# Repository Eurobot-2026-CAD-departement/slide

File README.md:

# Slide — final Eurobot 2026 robot

This repository contains the **official and final CAD** of the Eurobot 2026 Aerobotix robot.

The full assembly of the robot is `Slide final CAD.SLDASM` (stored with Git LFS). Each section of the design is in its own folder inside the assembly; folder and part names should be self-explanatory from there.

> For future reference: **zo7li9a = Slide** :)

## Contents
- `Slide final CAD.SLDASM`, `slide left/right.SLDASM`, `single slide complete.SLDASM`, `hinge left side.SLDASM` — assemblies
- `piece util/` — **most useful folder**: CAD of common pieces (motors, wheels, pumps, pneumatic fittings, ...). It will probably save you a lot of time. (Also available on its own as [slide-piece-util](https://github.com/Eurobot-2026-CAD-departement/slide-piece-util).)
- `3d printing/` — files for 3D printed parts
- `CNC lazer cutting/`, `CNC machining/` — laser-cutting and machining files / drawings
- `PCBs/` — KiCad projects of the electronics (MOSFET board, relay board, servo board, distribution board, ESP motors 2.0, PAMI ESP32, programming board, ...)
- `lidar support/`, `hinges/`, `pulley double action/`, `prototype/`, `essay 1/`, `missing_parts/` — sub-mechanisms and trials
- `slide urdf files/`, `URDFExporter/` — URDF export of the robot (SW2URDF)

Questions? Contact **Jihed Silini**.

Thank you for your attention to this file!

---

Part of the CAD work of the **Aerobotix (INSAT, Tunisia) Eurobot 2026 team** — see the [organization](https://github.com/Eurobot-2026-CAD-departement) for the other repositories. Files are mainly SolidWorks (`.SLDPRT` / `.SLDASM`) with STEP / STL / DXF exports. Released under the [MIT License](LICENSE). Questions about anything unclear? Contact a team member.

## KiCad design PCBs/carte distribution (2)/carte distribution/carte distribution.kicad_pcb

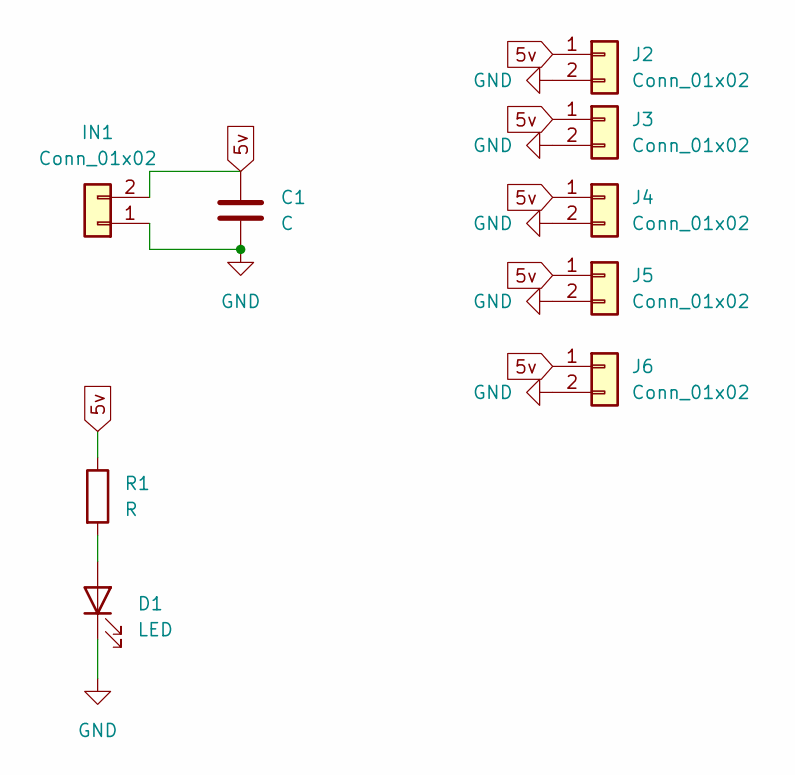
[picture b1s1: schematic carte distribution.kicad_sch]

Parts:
C1: C; C_Radial_D6.3mm_H5.0mm_P2.50mm
D1: LED; LED_D4.0mm
IN1: Conn_01x02; TerminalBlock_MaiXu_MX126-5.0-02P_1x02_P5.00mm
J2, J3, J4, J5, J6: Conn_01x02; TerminalBlock_MaiXu_MX126-5.0-02P_1x02_P5.00mm
R1: R; R_Axial_DIN0207_L6.3mm_D2.5mm_P7.62mm_Horizontal

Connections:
5v: C1.1, IN1.2, J2.1, J3.1, J4.1, J5.1, J6.1, R1.1
GND: C1.2, D1.1 (K), IN1.1, J2.2, J3.2, J4.2, J5.2, J6.2
unnamed: D1.2 (A), R1.2

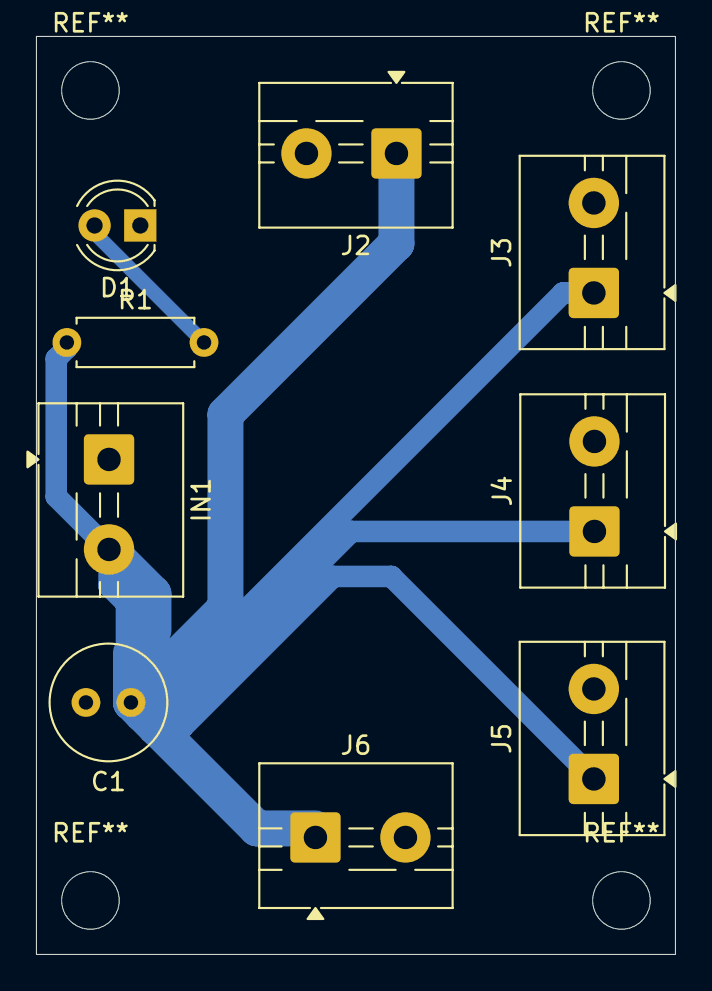
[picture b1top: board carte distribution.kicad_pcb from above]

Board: 2 copper layers, 35.5 x 51.0 mm, 9 parts (0 on the bottom side), 3 nets.

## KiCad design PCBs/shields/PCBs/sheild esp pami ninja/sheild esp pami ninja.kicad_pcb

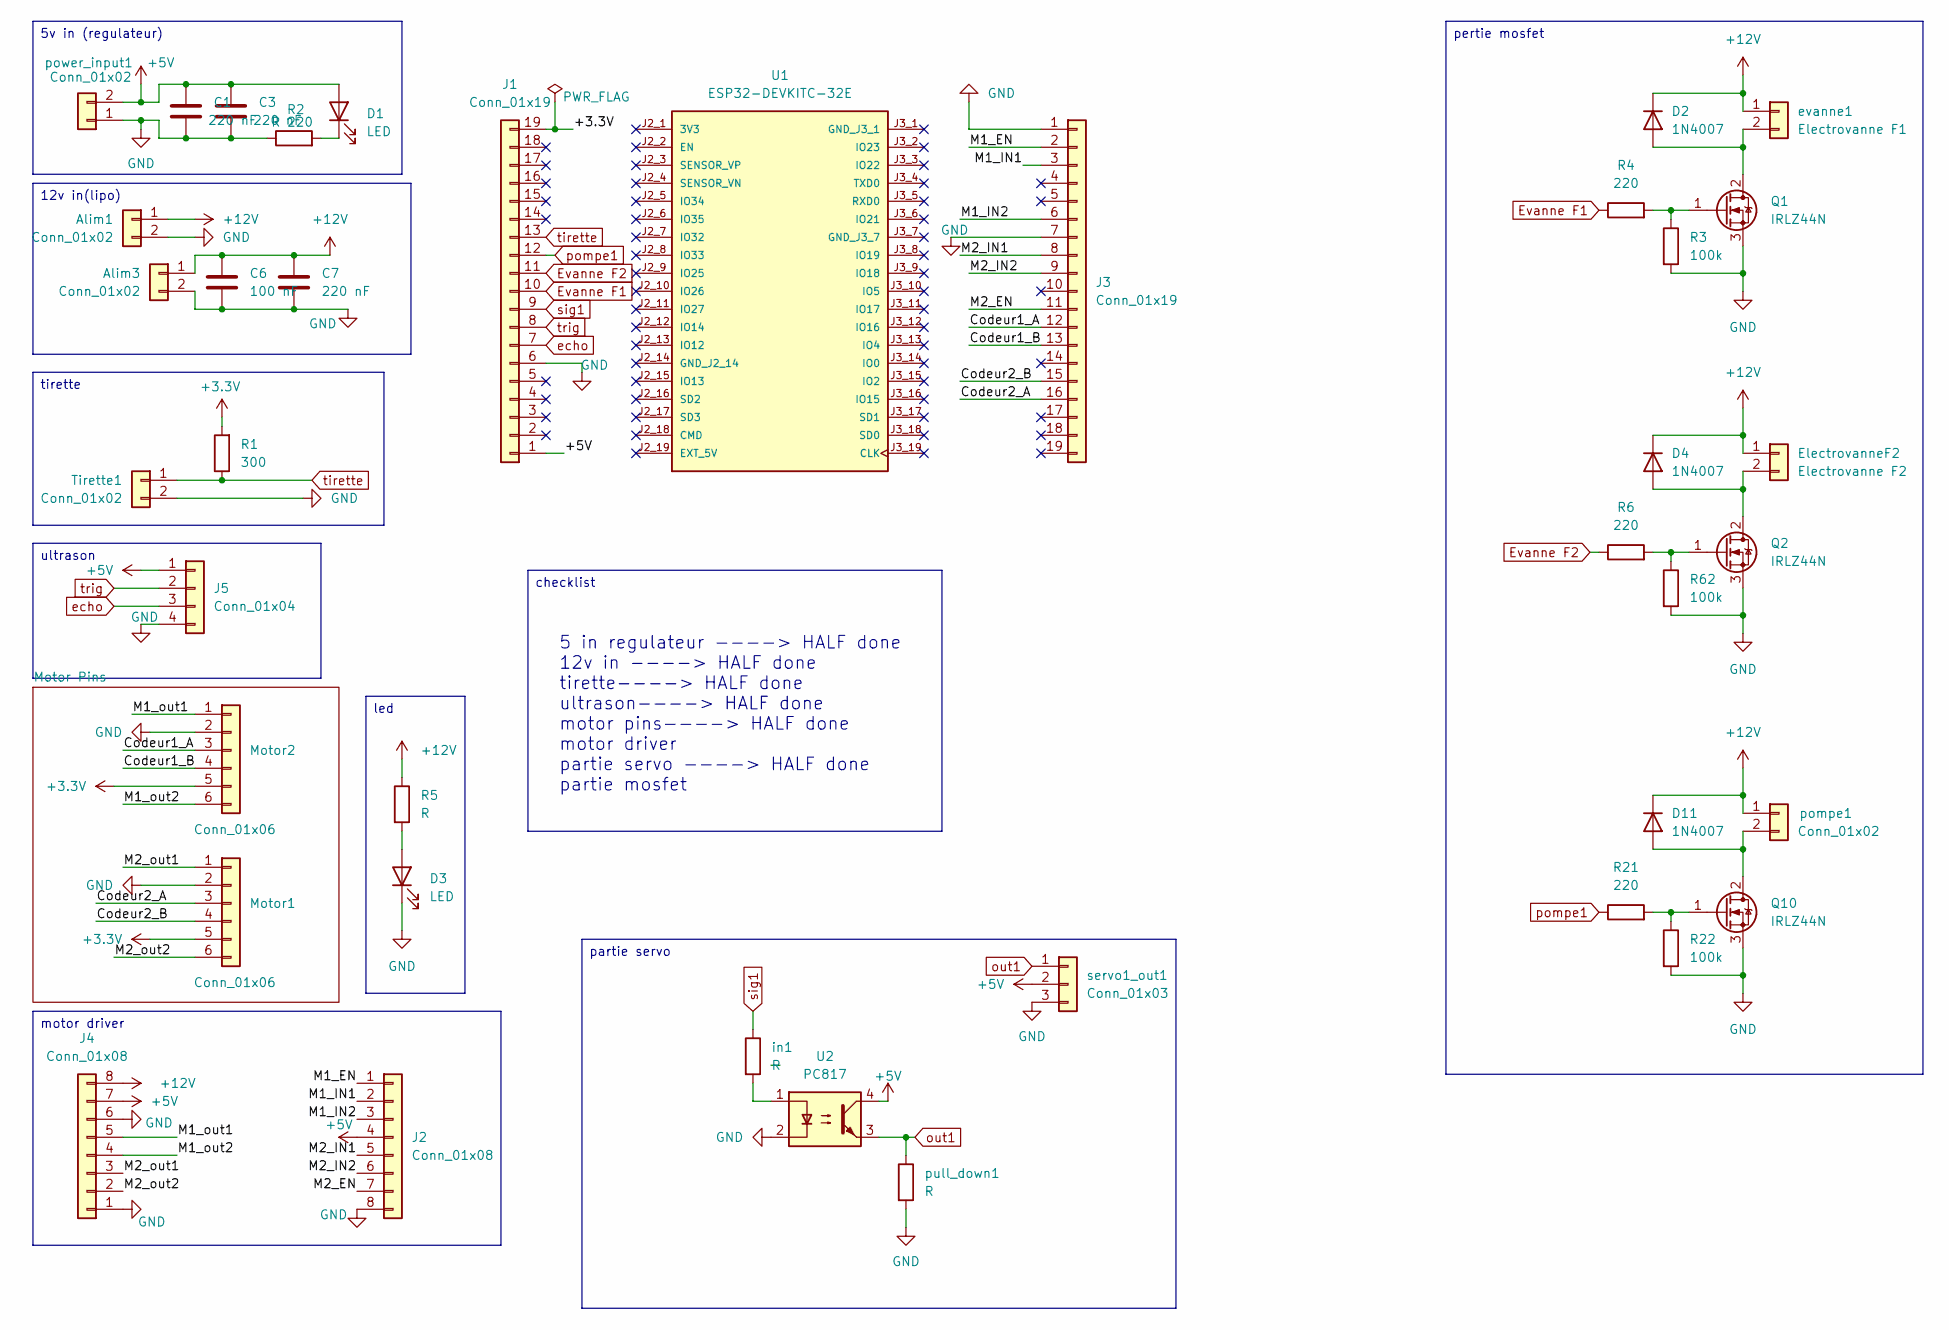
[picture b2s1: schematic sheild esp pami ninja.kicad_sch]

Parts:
Alim1, Alim3: Conn_01x02; TerminalBlock_MaiXu_MX126-5.0-02P_1x02_P5.00mm
C1, C3, C7: 220 nF; C_Radial_D6.3mm_H5.0mm_P2.50mm
C6: 100 nF; C_Radial_D6.3mm_H5.0mm_P2.50mm
D1, D3: LED; LED_D4.0mm
D2, D4, D11: 1N4007; D_DO-41_SOD81_P10.16mm_Horizontal
ElectrovanneF2: Electrovanne F2; JST_XH_B2B-XH-A_1x02_P2.50mm_Vertical
J1, J3: Conn_01x19; PinSocket_1x19_P2.54mm_Vertical
J2, J4: Conn_01x08; PinSocket_1x08_P2.54mm_Vertical
J5: Conn_01x04; PinHeader_1x04_P2.54mm_Vertical
Motor1, Motor2: Conn_01x06; PinHeader_1x06_P2.54mm_Vertical
Q1, Q2, Q10: IRLZ44N; TO-220-3_Vertical
R1: 300; R_Axial_DIN0207_L6.3mm_D2.5mm_P7.62mm_Horizontal
R2: R 220; R_Axial_DIN0207_L6.3mm_D2.5mm_P7.62mm_Horizontal
R3, R22, R62: 100k; R_Axial_DIN0207_L6.3mm_D2.5mm_P7.62mm_Horizontal
R4, R6, R21: 220; R_Axial_DIN0207_L6.3mm_D2.5mm_P7.62mm_Horizontal
R5: R; R_Axial_DIN0207_L6.3mm_D2.5mm_P7.62mm_Horizontal
Tirette1: Conn_01x02; PinHeader_1x02_P2.54mm_Vertical
U1: ESP32-DEVKITC-32E; PARTREV 1.4
U2: PC817; DIP-4_W7.62mm
evanne1: Electrovanne F1; JST_XH_B2B-XH-A_1x02_P2.50mm_Vertical
in1: R; R_Axial_DIN0207_L6.3mm_D2.5mm_P7.62mm_Horizontal
pompe1: Conn_01x02; JST_XH_B2B-XH-A_1x02_P2.50mm_Vertical
power_input1: Conn_01x02; TerminalBlock_MaiXu_MX126-5.0-02P_1x02_P5.00mm
pull_down1: R; R_Axial_DIN0207_L6.3mm_D2.5mm_P7.62mm_Horizontal
servo1_out1: Conn_01x03; PinHeader_1x03_P2.54mm_Vertical

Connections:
+3.3V: J1.19, Motor1.5, Motor2.5, R1.2
+5V: C1.1, C3.1, D1.2 (A), J1.1, J2.4, J4.7, J5.1, U2.4, power_input1.2, servo1_out1.2
+12V: Alim1.1, Alim3.1, C6.1, C7.1, D2.1 (K), D4.1 (K), D11.1 (K), ElectrovanneF2.1, J4.8, R5.1, evanne1.1, pompe1.1
/Codeur1_A: J3.12, Motor2.3
/Codeur1_B: J3.13, Motor2.4
/Codeur2_A: J3.16, Motor1.3
/Codeur2_B: J3.15, Motor1.4
/M1_EN: J2.1, J3.2
/M1_IN1: J2.2, J3.3
/M1_IN2: J2.3, J3.6
/M1_out1: J4.5, Motor2.1
/M1_out2: J4.4, Motor2.6
/M2_EN: J2.7, J3.11
/M2_IN1: J2.5, J3.8
/M2_IN2: J2.6, J3.9
/M2_out1: J4.3, Motor1.1
/M2_out2: J4.2, Motor1.6
Evanne F1: J1.10, R4.1
Evanne F2: J1.11, R6.1
GND: Alim1.2, Alim3.2, C1.2, C3.2, C6.2, C7.2, D3.1 (K), J1.6, J2.8, J3.1, J3.7, J4.1, J4.6, J5.4, Motor1.2, Motor2.2, Q1.3 (S), Q2.3 (S), Q10.3 (S), R2.1, R3.2, R22.2, R62.2, Tirette1.2, U2.2, power_input1.1, pull_down1.2, servo1_out1.3
unnamed: D1.1 (K), R2.2
unnamed: D2.2 (A), Q1.2 (D), evanne1.2
unnamed: D3.2 (A), R5.2
unnamed: D4.2 (A), ElectrovanneF2.2, Q2.2 (D)
unnamed: D11.2 (A), Q10.2 (D), pompe1.2
unnamed: Q1.1 (G), R3.1, R4.2
unnamed: Q2.1 (G), R6.2, R62.1
unnamed: Q10.1 (G), R21.2, R22.1
unnamed: U2.1, in1.2
echo: J1.7, J5.3
out1: U2.3, pull_down1.1, servo1_out1.1
pompe1: J1.12, R21.1
sig1: J1.9, in1.1
tirette: J1.13, R1.1, Tirette1.1
trig: J1.8, J5.2

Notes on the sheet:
5 in regulateur ----> HALF done 12v in ----> HALF done tirette----> HALF done ultrason----> HALF done motor pins----> HALF done motor driver partie servo ----> HALF done partie mosfet
pertie mosfet
5v in (regulateur)
checklist
ultrason
tirette
led
12v in(lipo)
partie servo
motor driver

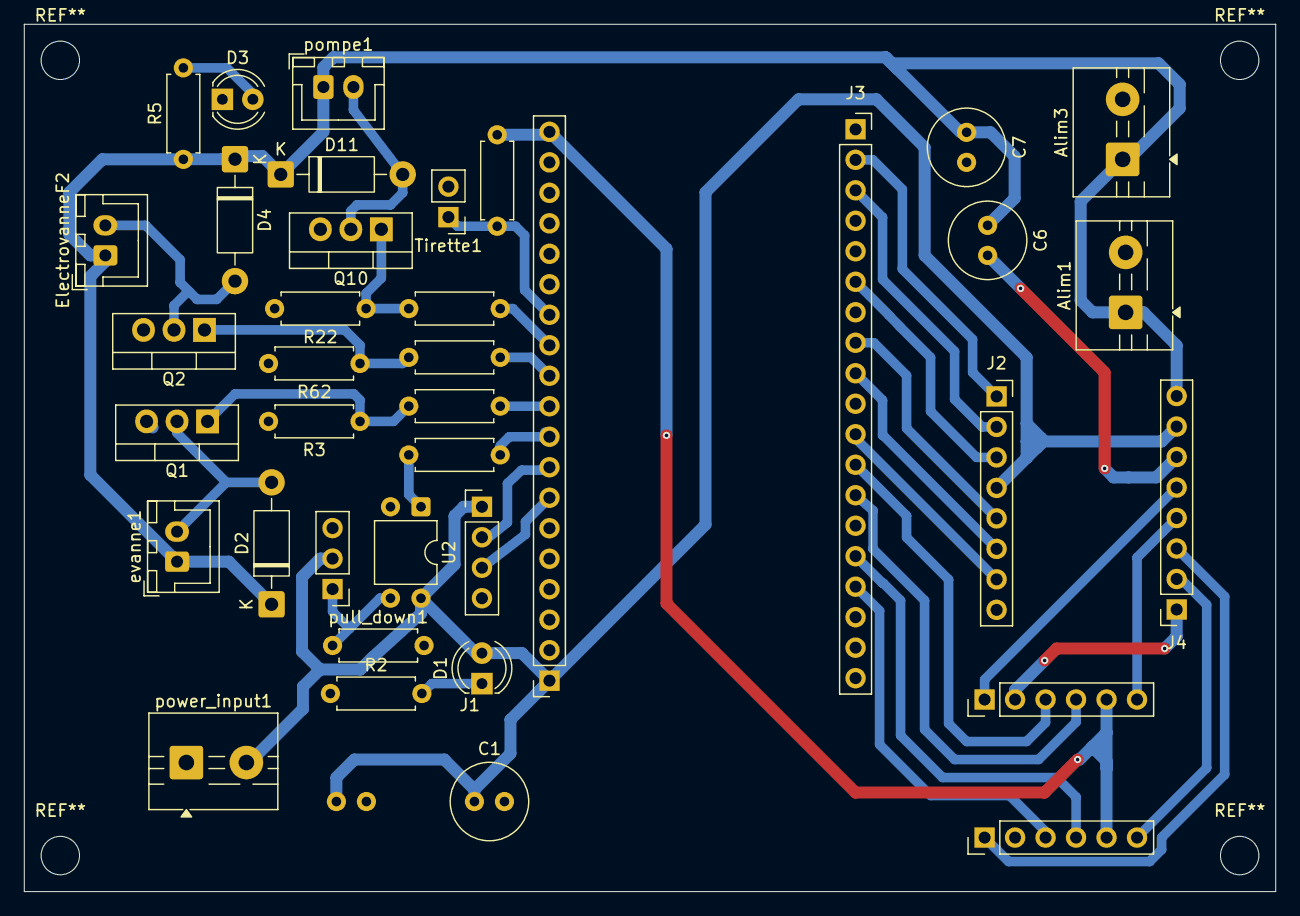
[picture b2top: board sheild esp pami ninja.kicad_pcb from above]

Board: 2 copper layers, 104.2 x 72.2 mm, 39 parts (1 on the bottom side), 35 nets.

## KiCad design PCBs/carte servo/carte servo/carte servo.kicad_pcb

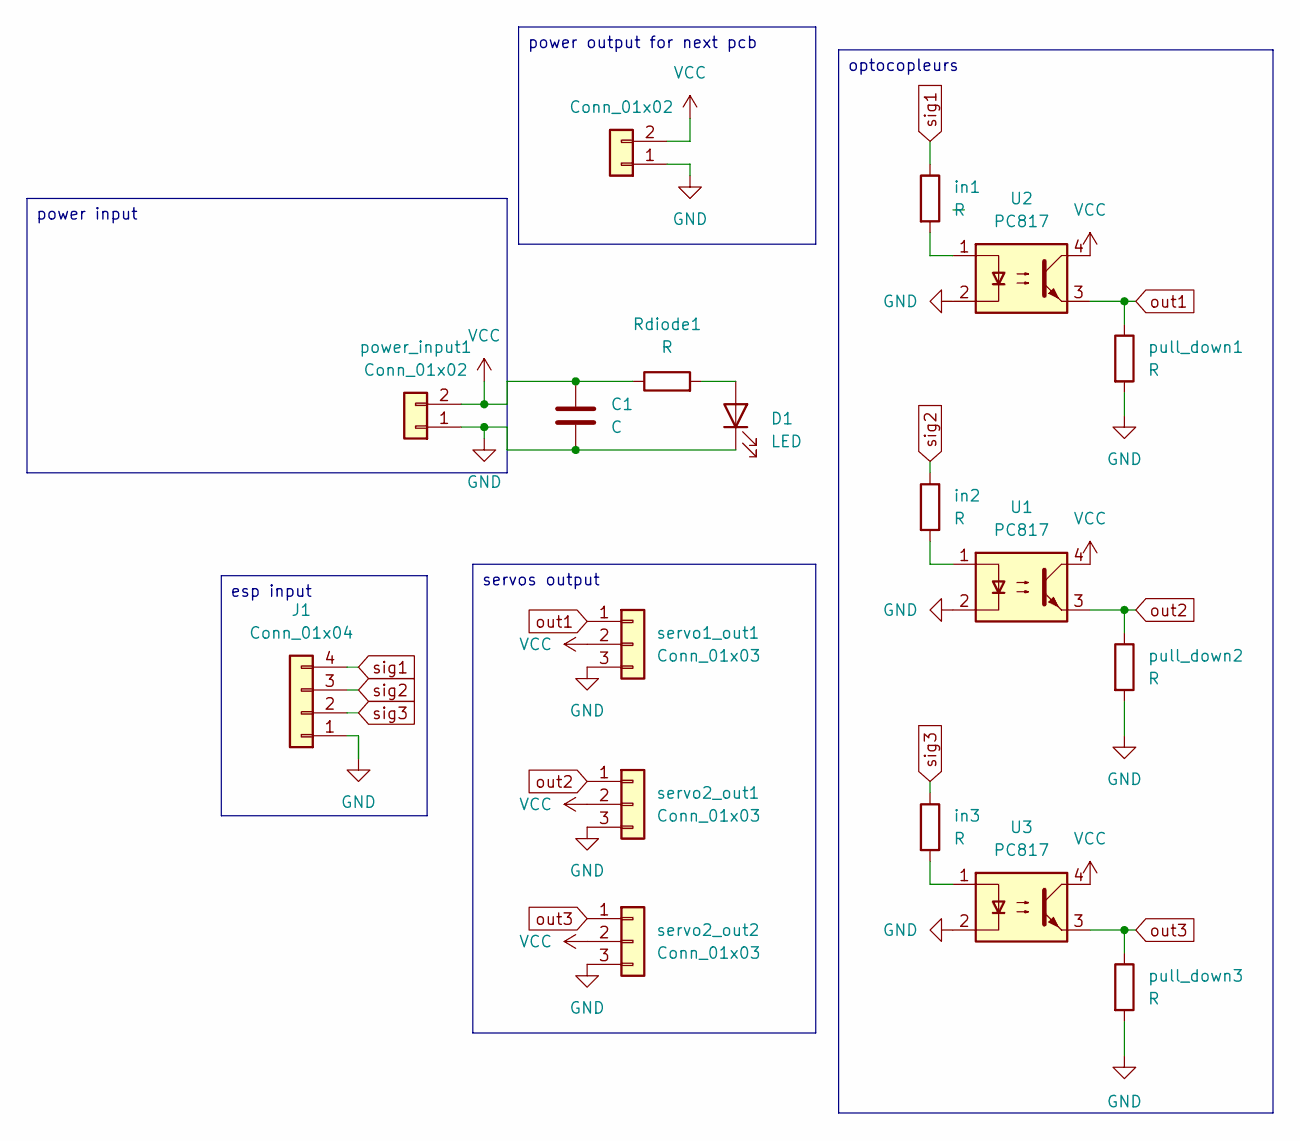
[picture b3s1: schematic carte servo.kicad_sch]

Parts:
C1: C; C_Radial_D6.3mm_H5.0mm_P2.50mm
D1: LED; LED_D4.0mm
J1: Conn_01x04; PinHeader_1x04_P2.54mm_Vertical
Rdiode1: R; R_Axial_DIN0207_L6.3mm_D2.5mm_P7.62mm_Horizontal
U1, U2, U3: PC817; DIP-4_W7.62mm
in1, in2, in3: R; R_Axial_DIN0207_L6.3mm_D2.5mm_P7.62mm_Horizontal
power_input1: Conn_01x02; TerminalBlock_MaiXu_MX126-5.0-02P_1x02_P5.00mm
power_output1: Conn_01x02; TerminalBlock_MaiXu_MX126-5.0-02P_1x02_P5.00mm
pull_down1, pull_down2, pull_down3: R; R_Axial_DIN0207_L6.3mm_D2.5mm_P7.62mm_Horizontal
servo1_out1, servo2_out1, servo2_out2: Conn_01x03; PinHeader_1x03_P2.54mm_Vertical

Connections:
GND: C1.2, D1.1 (K), J1.1, U1.2, U2.2, U3.2, power_input1.1, power_output1.1, pull_down1.2, pull_down2.2, pull_down3.2, servo1_out1.3, servo2_out1.3, servo2_out2.3
unnamed: D1.2 (A), Rdiode1.2
unnamed: U1.1, in2.2
unnamed: U2.1, in1.2
unnamed: U3.1, in3.2
VCC: C1.1, Rdiode1.1, U1.4, U2.4, U3.4, power_input1.2, power_output1.2, servo1_out1.2, servo2_out1.2, servo2_out2.2
out1: U2.3, pull_down1.1, servo1_out1.1
out2: U1.3, pull_down2.1, servo2_out1.1
out3: U3.3, pull_down3.1, servo2_out2.1
sig1: J1.4, in1.1
sig2: J1.3, in2.1
sig3: J1.2, in3.1

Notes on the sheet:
power input
optocopleurs
esp input
servos output
power output for next pcb

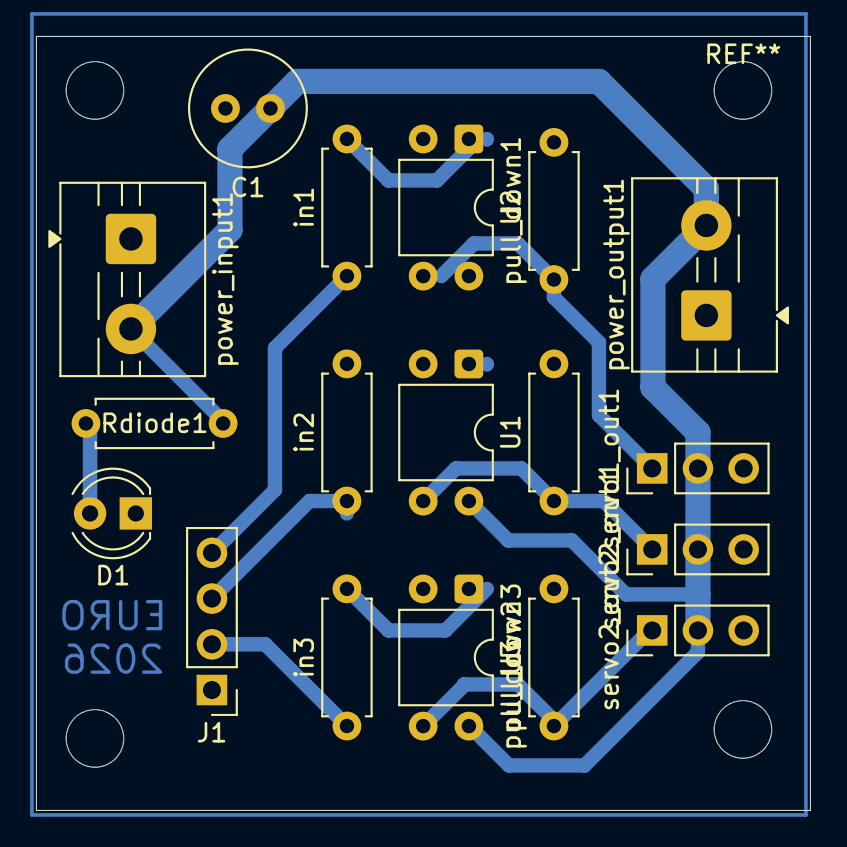
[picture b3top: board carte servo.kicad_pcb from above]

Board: 2 copper layers, 43.0 x 43.0 mm, 18 parts (0 on the bottom side), 12 nets.

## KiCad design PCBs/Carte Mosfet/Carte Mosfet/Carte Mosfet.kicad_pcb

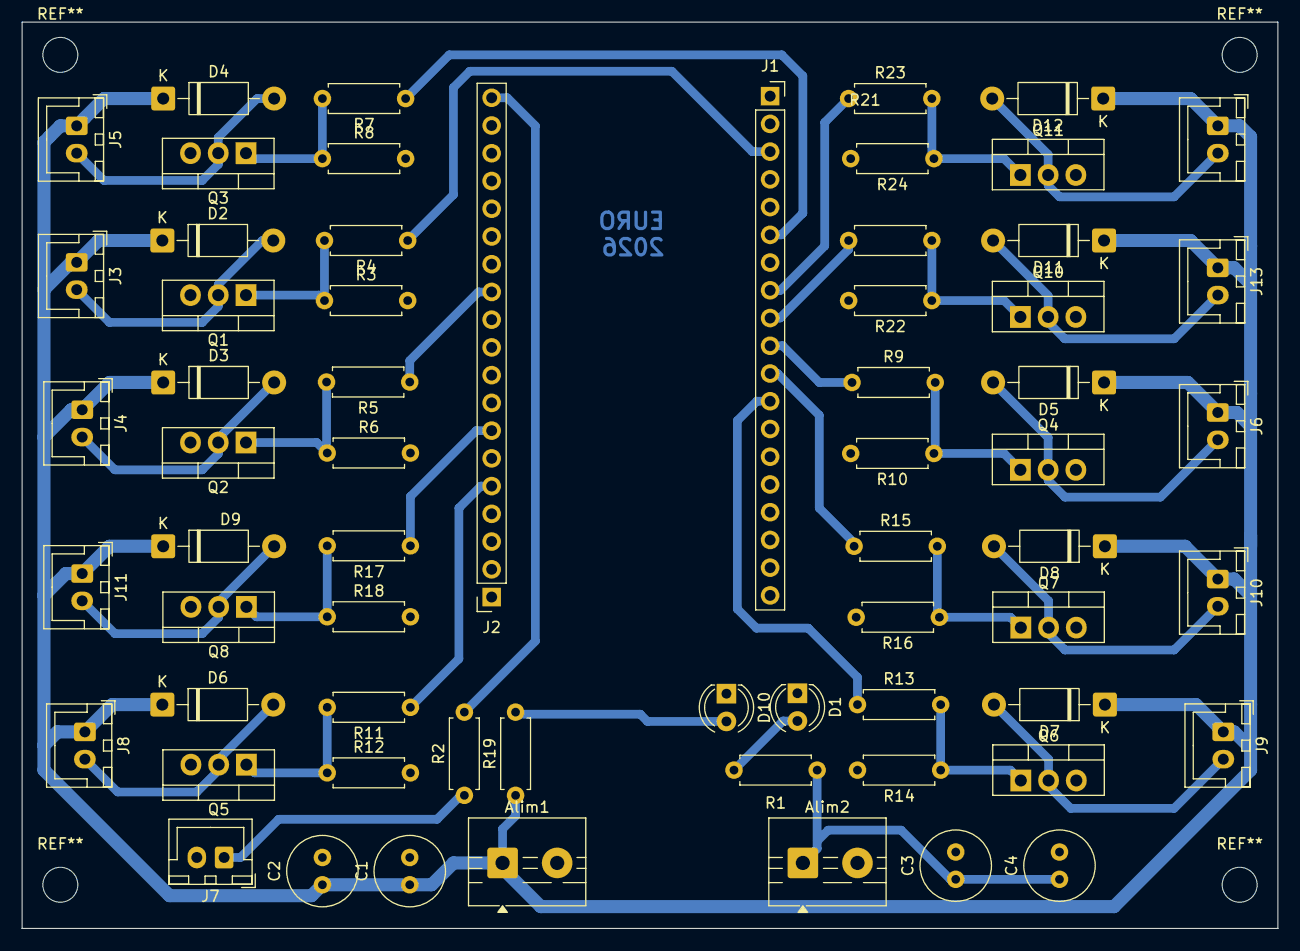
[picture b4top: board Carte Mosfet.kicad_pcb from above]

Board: 2 copper layers, 115.0 x 83.0 mm, 64 parts (0 on the bottom side), 37 nets.

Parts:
Alim1, Alim2: Conn_01x02; TerminalBlock_MaiXu_MX126-5.0-02P_1x02_P5.00mm
C1, C3: 100 nF; C_Radial_D6.3mm_H5.0mm_P2.50mm
C2, C4: 220 nF; C_Radial_D6.3mm_H5.0mm_P2.50mm
D1, D10: LED; LED_D4.0mm
D2, D3, D4, D5, D6, D7, D8, D9, D11, D12: 1N4007; D_DO-41_SOD81_P10.16mm_Horizontal
J1, J2: Conn_01x19; PinSocket_1x19_P2.54mm_Vertical
J3, J4, J5, J6, J8, J9, J10, J11, J13, J14: Conn_01x02; JST_XH_B2B-XH-A_1x02_P2.50mm_Vertical
J7: Conn_01x01; JST_XH_B2B-XH-A_1x02_P2.50mm_Vertical
Q1, Q2, Q3, Q4, Q5, Q6, Q7, Q8, Q10, Q11: IRLZ44N; TO-220-3_Vertical
R1, R19: R; R_Axial_DIN0207_L6.3mm_D2.5mm_P7.62mm_Horizontal
R2: 10k; R_Axial_DIN0207_L6.3mm_D2.5mm_P7.62mm_Horizontal
R3, R6, R8, R10, R12, R14, R16, R18, R22, R24: 100k; R_Axial_DIN0207_L6.3mm_D2.5mm_P7.62mm_Horizontal
R4, R5, R7, R9, R11, R13, R15, R17, R21, R23: 220; R_Axial_DIN0207_L6.3mm_D2.5mm_P7.62mm_Horizontal

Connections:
+3.3V: J2.19, R2.2
+5V: Alim2.1, C3.1, C4.1, J2.1, R1.1
+12V: Alim1.1, C1.1, C2.1, D2.1 (K), D3.1 (K), D4.1 (K), D5.1 (K), D6.1 (K), D7.1 (K), D8.1 (K), D9.1 (K), D11.1 (K), D12.1 (K), J3.1, J4.1, J5.1, J6.1, J8.1, J9.1, J10.1, J11.1, J13.1, J14.1, R19.1
Electrovanne B1: J2.5, R11.1
Electrovanne B2: J1.12, R13.1
Electrovanne B3: J1.11, R15.1
Electrovanne B4: J2.7, R17.1
Electrovanne F1: J1.3, R4.1
Electrovanne F2: J2.12, R5.1
Electrovanne F3: J1.6, R7.1
Electrovanne F4: J1.10, R9.1
GND: Alim1.2, Alim2.2, C1.2, C2.2, C3.2, C4.2, D1.1 (K), D10.1 (K), J1.1, J1.7, J2.6, Q1.3 (S), Q2.3 (S), Q3.3 (S), Q4.3 (S), Q5.3 (S), Q6.3 (S), Q7.3 (S), Q8.3 (S), Q10.3 (S), Q11.3 (S), R3.2, R6.2, R8.2, R10.2, R12.2, R14.2, R16.2, R18.2, R22.2, R24.2
unnamed: D1.2 (A), R1.2
unnamed: D2.2 (A), J3.2, Q1.2 (D)
unnamed: D3.2 (A), J4.2, Q2.2 (D)
unnamed: D4.2 (A), J5.2, Q3.2 (D)
unnamed: D5.2 (A), J6.2, Q4.2 (D)
unnamed: D6.2 (A), J8.2, Q5.2 (D)
unnamed: D7.2 (A), J9.2, Q6.2 (D)
unnamed: D8.2 (A), J10.2, Q7.2 (D)
unnamed: D9.2 (A), J11.2, Q8.2 (D)
unnamed: D10.2 (A), R19.2
unnamed: D11.2 (A), J13.2, Q10.2 (D)
unnamed: D12.2 (A), J14.2, Q11.2 (D)
unnamed: Q1.1 (G), R3.1, R4.2
unnamed: Q2.1 (G), R5.2, R6.1
unnamed: Q3.1 (G), R7.2, R8.1
unnamed: Q4.1 (G), R9.2, R10.1
unnamed: Q5.1 (G), R11.2, R12.1
unnamed: Q6.1 (G), R13.2, R14.1
unnamed: Q7.1 (G), R15.2, R16.1
unnamed: Q8.1 (G), R17.2, R18.1
unnamed: Q10.1 (G), R21.2, R22.1
unnamed: Q11.1 (G), R23.2, R24.1
Pump 1: J1.9, R21.1
Pump 2: J1.8, R23.1
en: J2.18, J7.1, R2.1

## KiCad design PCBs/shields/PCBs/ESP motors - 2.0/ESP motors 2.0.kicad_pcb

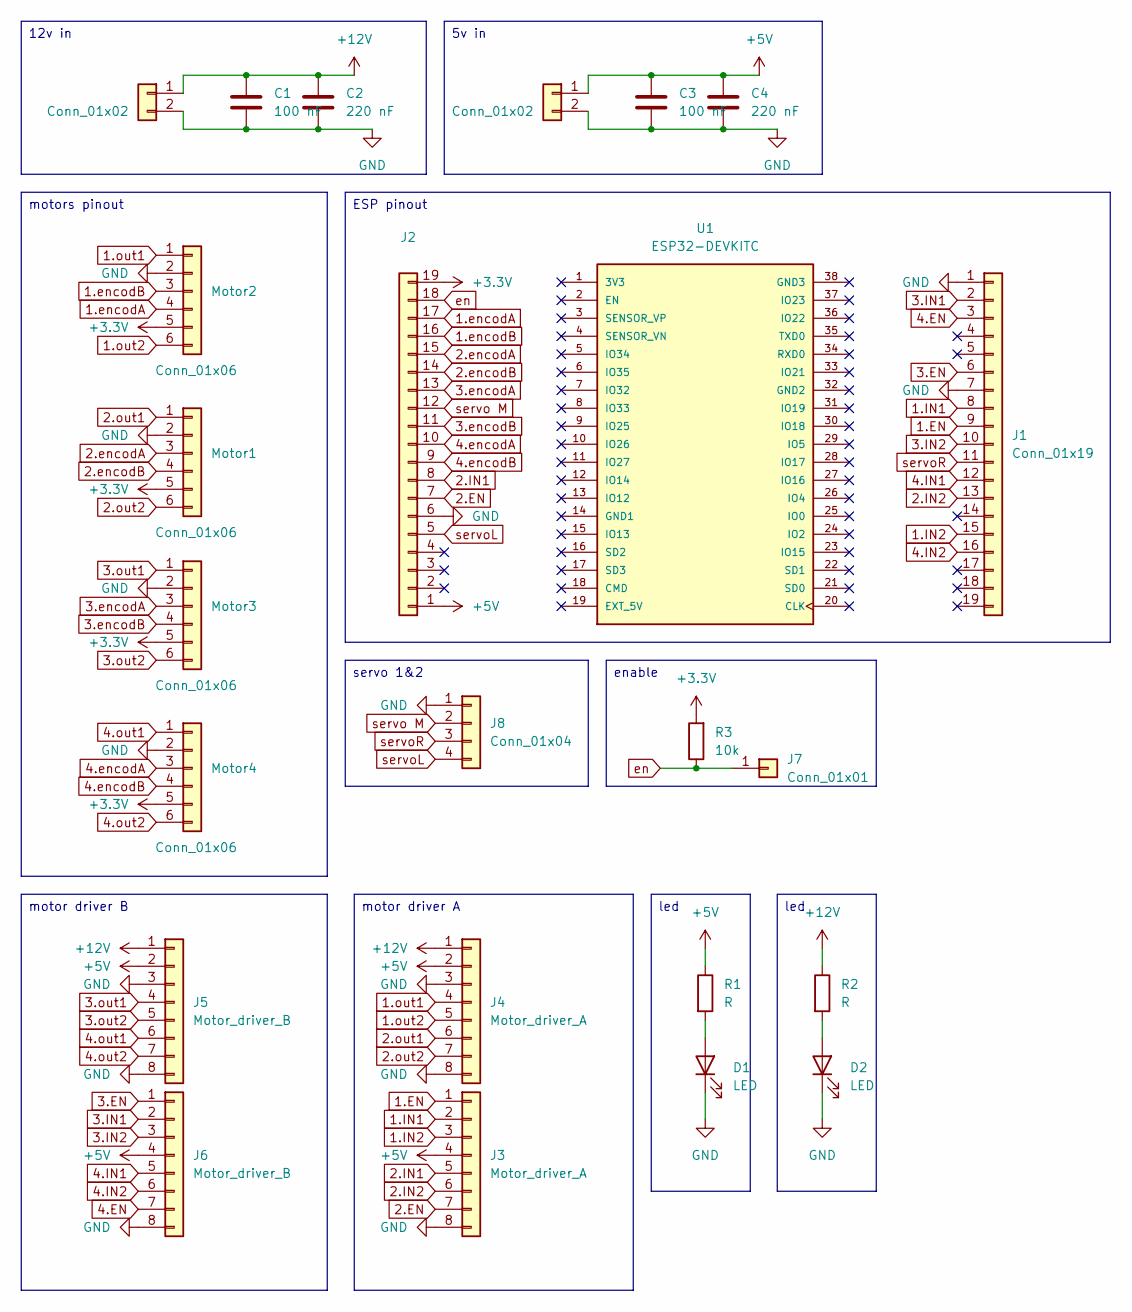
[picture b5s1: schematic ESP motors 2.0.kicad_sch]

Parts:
Alim1, Alim2: Conn_01x02; TerminalBlock_MaiXu_MX126-5.0-02P_1x02_P5.00mm
C1, C3: 100 nF; C_Radial_D6.3mm_H5.0mm_P2.50mm
C2, C4: 220 nF; C_Radial_D6.3mm_H5.0mm_P2.50mm
D1, D2: LED; LED_D4.0mm
J1, J2: Conn_01x19; PinSocket_1x19_P2.54mm_Vertical
J3, J4: Motor_driver_A; PinSocket_1x08_P2.54mm_Vertical
J5, J6: Motor_driver_B; PinSocket_1x08_P2.54mm_Vertical
J7: Conn_01x01; JST_XH_B2B-XH-A_1x02_P2.50mm_Vertical
J8: Conn_01x04; PinHeader_1x04_P2.54mm_Vertical
Motor1, Motor2, Motor3, Motor4: Conn_01x06; PinHeader_1x06_P2.54mm_Vertical
R1, R2: R; R_Axial_DIN0207_L6.3mm_D2.5mm_P7.62mm_Horizontal
R3: 10k; R_Axial_DIN0207_L6.3mm_D2.5mm_P7.62mm_Horizontal
U1: ESP32-DEVKITC; MODULE_ESP32-DEVKITC; PARTREV N/A

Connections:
1.EN: J1.9, J3.1
1.IN1: J1.8, J3.2
1.IN2: J1.15, J3.3
1.encodA: J2.17, Motor2.4
1.encodB: J2.16, Motor2.3
1.out1: J4.4, Motor2.1
1.out2: J4.5, Motor2.6
2.EN: J2.7, J3.7
2.IN1: J2.8, J3.5
2.IN2: J1.13, J3.6
2.encodA: J2.15, Motor1.3
2.encodB: J2.14, Motor1.4
2.out1: J4.6, Motor1.1
2.out2: J4.7, Motor1.6
3.EN: J1.6, J6.1
3.IN1: J1.2, J6.2
3.IN2: J1.10, J6.3
3.encodA: J2.13, Motor3.3
3.encodB: J2.11, Motor3.4
3.out1: J5.4, Motor3.1
3.out2: J5.5, Motor3.6
4.EN: J1.3, J6.7
4.IN1: J1.12, J6.5
4.IN2: J1.16, J6.6
4.encodA: J2.10, Motor4.3
4.encodB: J2.9, Motor4.4
4.out1: J5.6, Motor4.1
4.out2: J5.7, Motor4.6
+3.3V: J2.19, Motor1.5, Motor2.5, Motor3.5, Motor4.5, R3.2
+5V: Alim2.1, C3.1, C4.1, J2.1, J3.4, J4.2, J5.2, J6.4, R1.1
+12V: Alim1.1, C1.1, C2.1, J4.1, J5.1, R2.1
GND: Alim1.2, Alim2.2, C1.2, C2.2, C3.2, C4.2, D1.1 (K), D2.1 (K), J1.1, J1.7, J2.6, J3.8, J4.3, J4.8, J5.3, J5.8, J6.8, J8.1, Motor1.2, Motor2.2, Motor3.2, Motor4.2
unnamed: D1.2 (A), R1.2
unnamed: D2.2 (A), R2.2
en: J2.18, J7.1, R3.1
servo M: J2.12, J8.2
servoL: J2.5, J8.4
servoR: J1.11, J8.3

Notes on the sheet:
motor driver B
led
12v in
5v in
enable
motor driver A
servo 1&2
motors pinout
ESP pinout

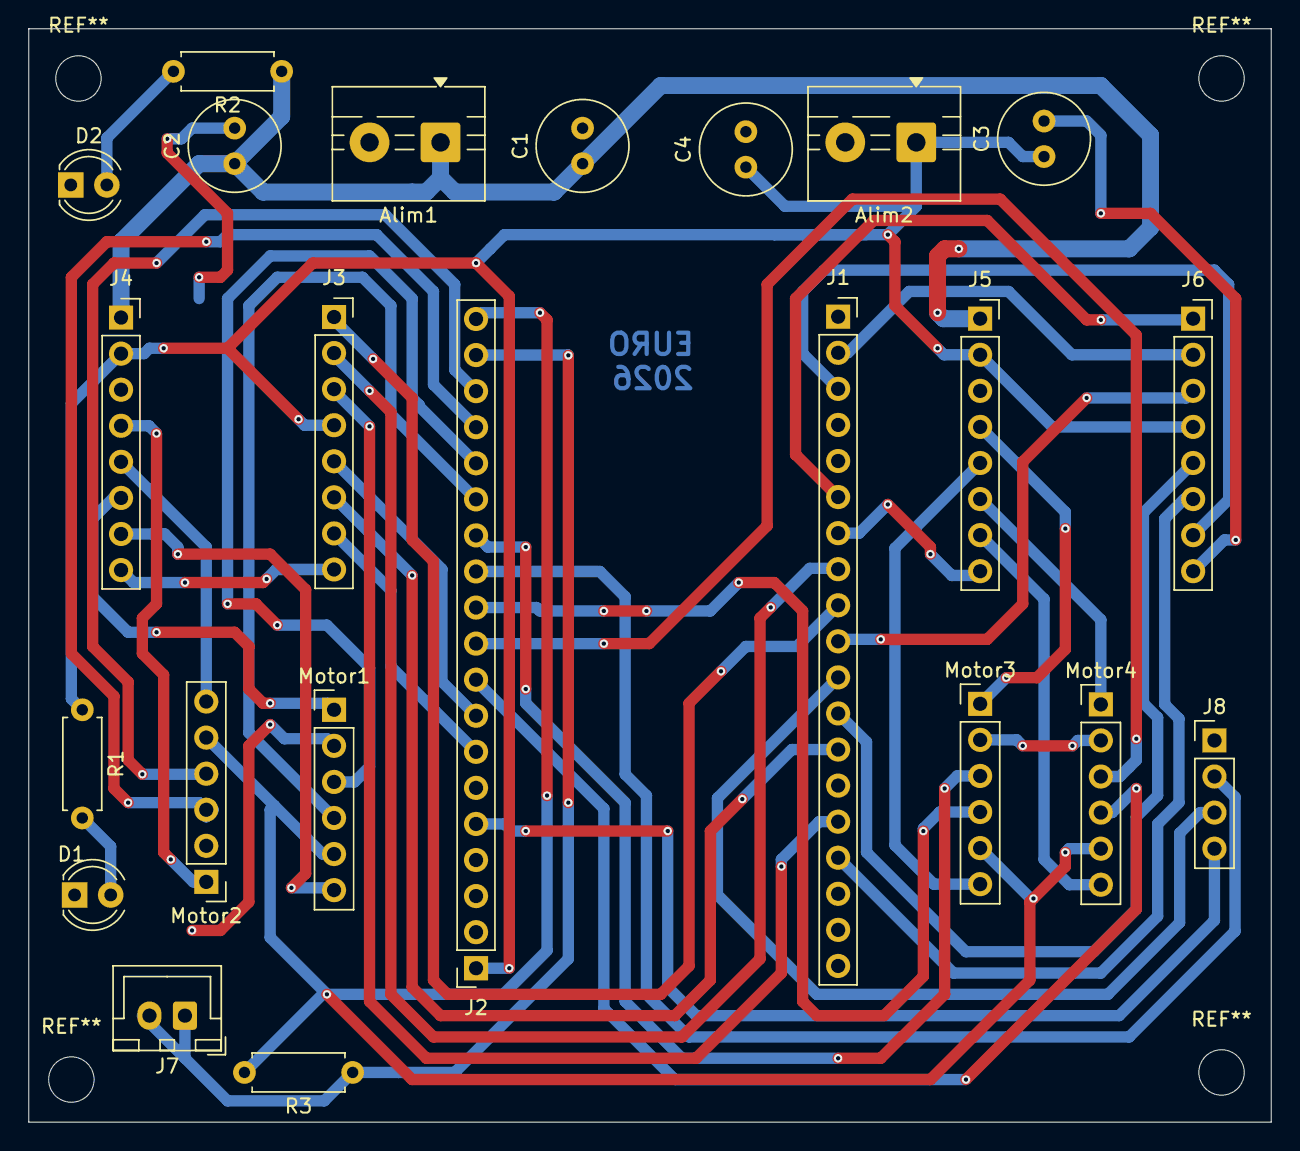
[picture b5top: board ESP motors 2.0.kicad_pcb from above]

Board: 2 copper layers, 87.5 x 77.0 mm, 23 parts (0 on the bottom side), 38 nets.
